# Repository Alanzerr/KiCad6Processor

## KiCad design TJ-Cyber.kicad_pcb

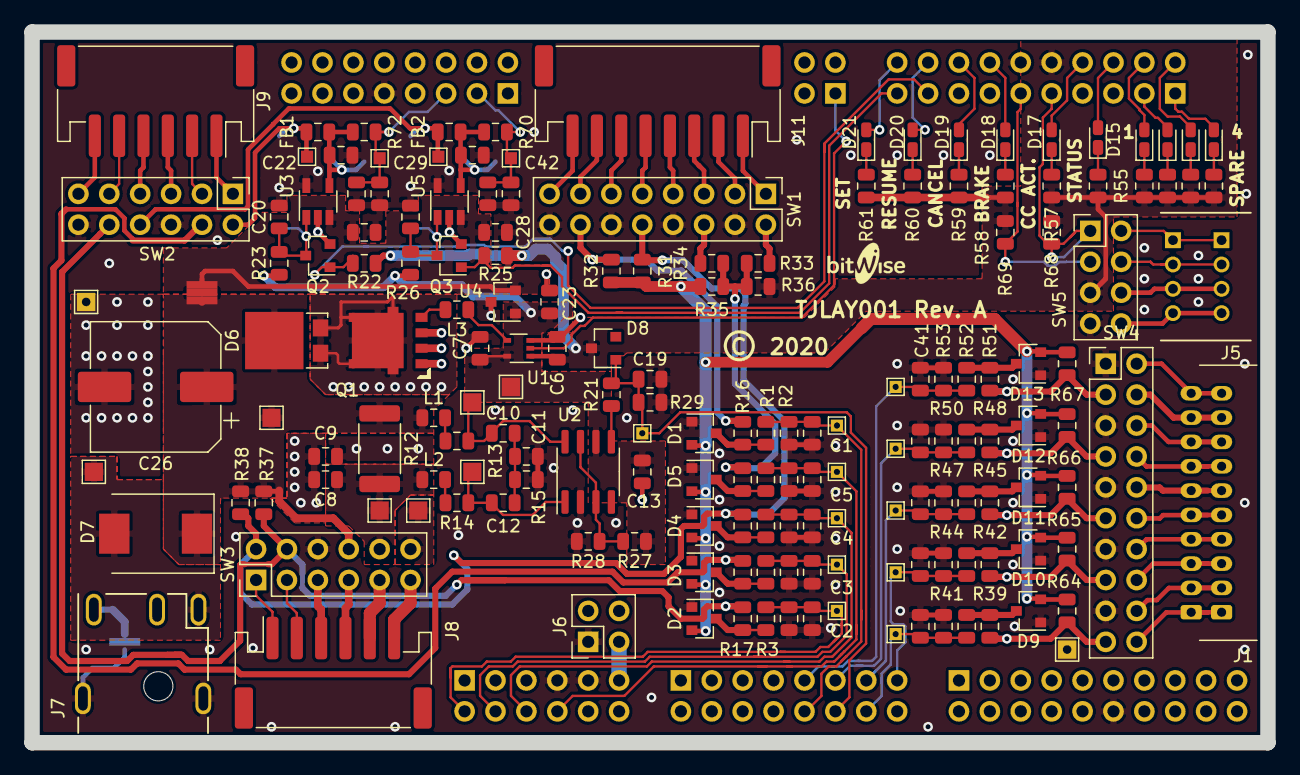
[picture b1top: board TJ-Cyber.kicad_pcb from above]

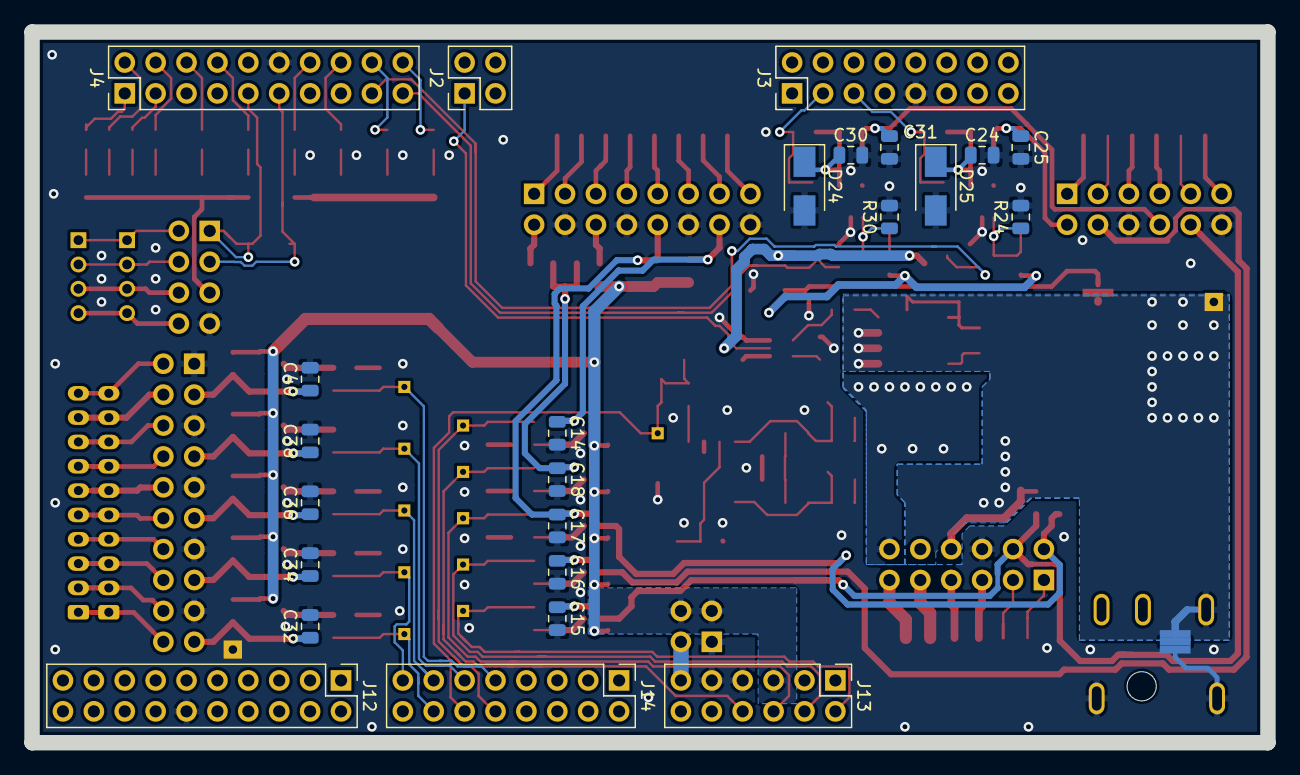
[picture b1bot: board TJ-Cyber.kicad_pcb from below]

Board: 2 copper layers, 101.6 x 58.4 mm, 235 parts (25 on the bottom side), 120 nets.

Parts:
BRD1: DNF; ProcessorStack
C1, C2, C3, C4, C5, C6, C7, C13, C20, C21, C27, C28, C33, C35, C37, C39, C41, C42, C43: 0.1uF; C_0805_2012Metric
C8, C9: 47nF; C_0805_2012Metric
C10, C12: 1nF; C_0805_2012Metric
C11, C14, C15, C16, C17, C18, C24, C25, C30, C31, C32, C34, C36, C38, C40: DNF; C_0805_2012Metric
C19: 390pF; C_0805_2012Metric
C22, C23, C29: 1uF; C_0805_2012Metric
C26: 100uF; CP_Elec_10x10.5
D1, D2, D3, D4, D5, D9, D10, D11, D12, D13: BAT54S; SOT-23
D6: SS8PH10; TO-277A
D7: MBRS540T3G; D_SMC
D8: BAR42FILM; SOT-23
D14: KPT-1608SURCK; LED_0603_1608Metric_Castellated
D15, D23: LSTS-C190GKT; LED_0603_1608Metric_Castellated
D16, D17, D18, D19, D20, D21, D22: LSTS-C190YKT; LED_0603_1608Metric_Castellated
D24, D25: DNF; D_SMA
FB1, FB2: 50mR; L_0805_2012Metric
J1: B10B-PH-K-S; JST_PH_B10B-PH-K_1x10_P2.00mm_Vertical_Hybrid
J2, J6: M20-9980245; PinHeader_2x02_P2.54mm_Vertical
J3, J14: M20-9980845; PinHeader_2x08_P2.54mm_Vertical
J4, J12: M20-9981045; PinHeader_2x10_P2.54mm_Vertical
J5: 110990030; Grove_1x4_P2mm_Vertical_Seeed_110990030_Hybrid
J7: PJ-051A; CUI_PJ-051A
J8, J9: S6B-PH-SM4-TB; JST_PH_S6B-PH-SM4-TB_1x06-1MP_P2.00mm_Horizontal
J11: S8B-PH-SM4-TB; JST_PH_S8B-PH-SM4-TB_1x08-1MP_P2.00mm_Horizontal
J13: M20-9980645; PinHeader_2x06_P2.54mm_Vertical
JMP1, JMP2, JMP3, JMP4, JMP5, JMP6, JMP7, JMP8, JMP9, JMP10, JMP11, JMP12, JMP13, JMP14, JMP15, JMP16, JMP17, JMP18, JMP19, JMP20, JMP21, JMP22, JMP23, JMP24, JMP25, JMP26, JMP27, JMP28, JMP29, JMP30, JMP31, JMP32, JMP33, JMP34: Shunt; Dummy_Jumper_Footprint_for_BOM
L1, L2, L3: 1KR; L_0805_2012Metric
LB1: DNF; BitwiseLogo
LB2: DNF; COPYRIGHT_2020
NT1, NT2: DNF; NetTie-2_SMD_Pad25mil
Q1: NVMFS5C460NL; DFN5
Q2, Q3: MGSF1N03LT1G; SOT-23
R1, R3, R5, R7, R9, R29, R40, R43, R46, R49, R52: 2K; R_0805_2012Metric
R2, R4, R6, R8, R10, R27, R41, R44, R47, R50, R53, R68, R69, R71, R73: 4.7K; R_0805_2012Metric
R11, R22, R25, R31, R32, R37, R38, R64, R65, R66, R67: 10K; R_0805_2012Metric
R12: 0.05R; R_2512_6332Metric
R13, R14: 10R; R_0805_2012Metric
R15: 33R; R_0805_2012Metric
R16, R17, R18, R19, R20, R39, R42, R45, R48, R51: 1.1K; R_0805_2012Metric
R21, R23, R26: 1K; R_0805_2012Metric
R24, R30: DNF; R_0805_2012Metric
R28: 100R; R_0805_2012Metric
R33, R35: 330R; R_0805_2012Metric
R34, R36: 680R; R_0805_2012Metric
R54, R56, R57, R58, R59, R60, R61, R62: 270R; R_0805_2012Metric
R55, R63: 220R; R_0805_2012Metric
R70, R72: 3.3K; R_0805_2012Metric
SW1: M20-9980845; PinHeader_2x08_P2.54mm_Vertical_Shunts
SW2, SW3: M20-9980645; PinHeader_2x06_P2.54mm_Vertical_Shunts
SW4: M20-9981045; PinHeader_2x10_P2.54mm_Vertical_Shunts
SW5: M20-9980445; PinHeader_2x04_P2.54mm_Vertical_Shunts
TP1, TP2, TP21, TP22: DNF; TestPoint_Pad_1.0x1.0mm
TP7, TP8, TP9, TP10, TP11, TP12, TP33, TP34, TP35, TP36, TP37: DNF; TestPoint_THTPad_1.0x1.0mm_Drill0.5mm
TP13, TP14: DNF; TestPoint_THTPad_1.5x1.5mm_Drill0.7mm
TP15, TP16, TP17, TP18, TP19, TP20, TP23: DNF; TestPoint_Pad_1.5x1.5mm
U1: SN74AUP1T34DCK; SOT-353_SC-70-5
U2: AD8210; SOIC-8_3.9x4.9mm_P1.27mm
U3, U5: NCV4250−2CSNT1G; TSOT-23-5
U4: ZMR500F; SOT-23

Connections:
+3V3: C6.1, D8.3, J4.10, R22.1, R25.1, R54.1, R55.1, R56.1, R57.1, R58.1, R59.1, R60.1, R61.1, R62.1, R63.1, R68.1, R69.1, SW5.5, U1.1
+5V: C7.1, C13.1, C23.1, R23.1, R26.1, R27.1, TP23.1, U1.5, U2.6, U4.1
+5VA: D1.2, D2.2, D3.2, D4.2, D5.2, D9.2, D10.2, D11.2, D12.2, D13.2, J6.2, J6.4, J13.5, R11.1, R31.1, R32.1, R35.1, R64.1, R65.1, R66.1, R67.1
+12C: J6.3, J13.11
+12LF: C21.1, C28.1, NT1.2, U3.3, U4.2, U5.3
+12V: C26.1, D6.3, D7.1, L1.1, NT1.1, R12.1, R37.1, R38.1, SW3.8, TP20.1
+BATT: D7.2, J7.1, TP15.1
/ADC_CH1: C18.1, R20.2, R33.1, R34.1, R35.2, R36.1
/ADC_CH2: C17.1, R19.2, R31.2, R38.2, SW1.10, SW3.2
/ADC_CH3: C16.1, R18.2, SW2.4
/ADC_CH4: C15.1, R17.2, R37.2, SW2.10, SW3.4
/ADC_CH5: C14.1, R16.2, R32.2, SW1.14
/ADC_CH6: C40.1, R51.2, R67.2, SW4.3
/ADC_CH7: C38.1, R48.2, R66.2, SW4.7
/ADC_CH8: C36.1, R45.2, R65.2, SW4.11
/ADC_CH9: C34.1, R42.2, R64.2, SW4.15
/ADC_CH10: C32.1, R11.2, R39.2, SW4.19
/BRAKE: J11.7, SW1.13
/BRAKE_GND: J11.8, SW1.15
/CANCEL: J11.5, SW1.9
/CANCEL_GND: J11.6, SW1.11
/DRIVE+: C8.1, L2.1, R12.2, SW3.10, TP16.1
/DRIVE-: C9.1, D6.1, D6.2, Q1.5, SW3.12, TP17.1
/Driver/FIL_PWM: L3.2, Q1.4
/Driver/I_OUT: R21.1, U2.5
/Driver/I_SENSE+: C10.1, R13.1, TP18.1, U2.8
/Driver/I_SENSE-: C12.1, R14.1, TP19.1, U2.1
/Driver/PWM: L3.1, U1.4
/Driver/VREF: R27.2, R28.1, U2.3, U2.7
/GGND: J5.4, SW5.8
/GPWR: J5.3, SW5.6
/GSCL: J5.1, SW5.2
/GSDA: J5.2, SW5.4
/HallSensorAVout: J8.2, SW3.3
/HallSensorBVout: J8.1, SW3.1
/HallSensorGnd: J8.3, SW3.5
/HallSensorVcc: J8.4, SW3.7
/Motor+: J8.5, SW3.9
/Motor-: J8.6, SW3.11
/PA6_PWM: J2.1, U1.2
/PC10_STATUS_LED: D15.2, J4.6
/PC11_CCA_LED: D17.2, J4.8
/PD0_ADC1_P[4]: C1.1, J14.10, R1.2, R2.1, TP11.1
/PD1_ADC1_P[5]: C19.1, D8.1, J14.12, R21.2, R29.1, TP12.1
/PD2_ADC1_P[6]: C33.1, J14.14, R40.2, R41.1, TP33.1
/PE0_CANCEL_LED: D19.2, J4.16
/PE1_BRAKE_LED: D18.2, J4.14
/PE4_RESUME_LED: D20.2, J4.18
/PE5_SET_LED: D21.2, J4.20
/PF0_ADC0_S[8]: C42.1, J3.3, R70.2, R71.1, TP1.1
/PF1_PSU1_ADC0_S[9]: C43.1, J3.5, R72.2, R73.1, TP2.1
/PF4_ADC0_S[12]: C3.1, J13.4, R5.2, R6.1, TP8.1
/PF5_ADC0_S[13]: C4.1, J13.6, R7.2, R8.1, TP9.1
/PF6_ADC0_S[14]: C2.1, J13.2, R3.2, R4.1, TP7.1
/PF7_ADC0_S[15]: C5.1, J13.8, R9.2, R10.1, TP10.1
/PF12_PSU2_ENABLE: J4.19, Q3.1, R25.2
/PF13_PSU1_ENABLE: J4.17, Q2.1, R22.2
/PG2_SPARE3_LED: D22.2, J4.2
/PG3_SPARE4_LED: D23.2, J4.1
/PG4_SPARE2_LED: D16.2, J4.3
/PG5_SPARE1_LED: D14.2, J4.4
/PI2_SDA: J4.11, R69.2, SW5.3
/PI3_SCL: J4.9, R68.2, SW5.1
/PI12_ADC0_S[20]: C41.1, J14.9, R52.2, R53.1, TP37.1
/PI13_ADC0_S[21]: C39.1, J14.11, R49.2, R50.1, TP36.1
/PI14_ADC0_S[22]: C37.1, J14.13, R46.2, R47.1, TP35.1
/PI15_ADC0_S[23]: C35.1, J14.15, R43.2, R44.1, TP34.1
/POTA_GND: J9.3, SW2.5
/POTA_INPUT: J9.2, SW2.3
/POTA_PSU: J9.1, SW2.1
/POTB_GND: J9.6, SW2.11
/POTB_INPUT: J9.5, SW2.9
/POTB_PSU: J9.4, SW2.7
/PSU1: C25.1, FB1.1, SW2.2, TP21.1
/PSU1/EN: C20.1, Q2.3, R23.2, R24.1, U3.1
/PSU1/SENSOR_POWER: C22.1, C24.1, D25.1, FB1.2, R72.1, U3.4
/PSU2: C31.1, FB2.1, SW2.8, TP22.1
/PSU2/EN: C27.1, Q3.3, R26.2, R30.1, U5.1
/PSU2/SENSOR_POWER: C29.1, C30.1, D24.1, FB2.2, R70.1, U5.4
/RESUME: J11.3, SW1.5
/RESUME_GND: J11.4, SW1.7
/RI: R34.2, SW1.6
/SET: J11.1, SW1.1
/SET_GND: J11.2, SW1.3
/SI: R33.2, SW1.2
/SPARE1: J1.9, SW4.4
/SPARE1_GND: J1.10, SW4.2
/SPARE2: J1.7, SW4.8
/SPARE2_GND: J1.8, SW4.6
/SPARE3: J1.5, SW4.12
/SPARE3_GND: J1.6, SW4.10
/SPARE4: J1.3, SW4.16
/SPARE4_GND: J1.4, SW4.14
/SPARE5: J1.1, SW4.20
/SPARE5_GND: J1.2, SW4.18
GND: C1.2, C2.2, C3.2, C4.2, C5.2, C6.2, C7.2, C11.2, C13.2, C14.2, C15.2, C16.2, C17.2, C18.2, C19.2, C20.2, C21.2, C22.2, C23.2, C24.2, C25.2, C27.2, C28.2, C29.2, C30.2, C31.2, C32.2, C33.2, C34.2, C35.2, C36.2, C37.2, C38.2, C39.2, C40.2, C41.2, C42.2, C43.2, D1.1, D2.1, D3.1, D4.1, D5.1, D9.1, D10.1, D11.1, D12.1, D13.1, D24.2, D25.2, J3.9, J4.12, J6.1, J7.5, J7.6, J12.12, J13.7, J13.9, NT2.2, Q2.2, Q3.2, R2.2, R4.2, R6.2, R8.2, R10.2, R15.2, R24.2, R28.2, R29.2, R30.2, R36.2, R41.2, R44.2, R47.2, R50.2, R53.2, R71.2, R73.2, SW1.4, SW1.8, SW1.12, SW1.16, SW2.6, SW2.12, SW3.6, SW4.1, SW4.5, SW4.9, SW4.13, SW4.17, SW5.7, TP13.1, U1.3, U2.2, U3.2, U3.5, U4.3, U5.2, U5.5
GNDPWR: C8.2, C9.2, C26.2, J7.2, NT2.1, Q1.1, Q1.2, Q1.3, TP14.1
unnamed: C10.2, C11.1, C12.2, R15.1
unnamed: D1.3, R1.1, R16.1
unnamed: D2.3, R3.1, R17.1
unnamed: D3.3, R5.1, R18.1
unnamed: D4.3, R7.1, R19.1
unnamed: D5.3, R9.1, R20.1
unnamed: D9.3, R39.1, R40.1
unnamed: D10.3, R42.1, R43.1
unnamed: D11.3, R45.1, R46.1
unnamed: D12.3, R48.1, R49.1
unnamed: D13.3, R51.1, R52.1
unnamed: D14.1, R54.2
unnamed: D15.1, R55.2
unnamed: D16.1, R56.2
unnamed: D17.1, R57.2
unnamed: D18.1, R58.2
unnamed: D19.1, R59.2
unnamed: D20.1, R60.2
unnamed: D21.1, R61.2
unnamed: D22.1, R62.2
unnamed: D23.1, R63.2
unnamed: L1.2, R13.2
unnamed: L2.2, R14.2

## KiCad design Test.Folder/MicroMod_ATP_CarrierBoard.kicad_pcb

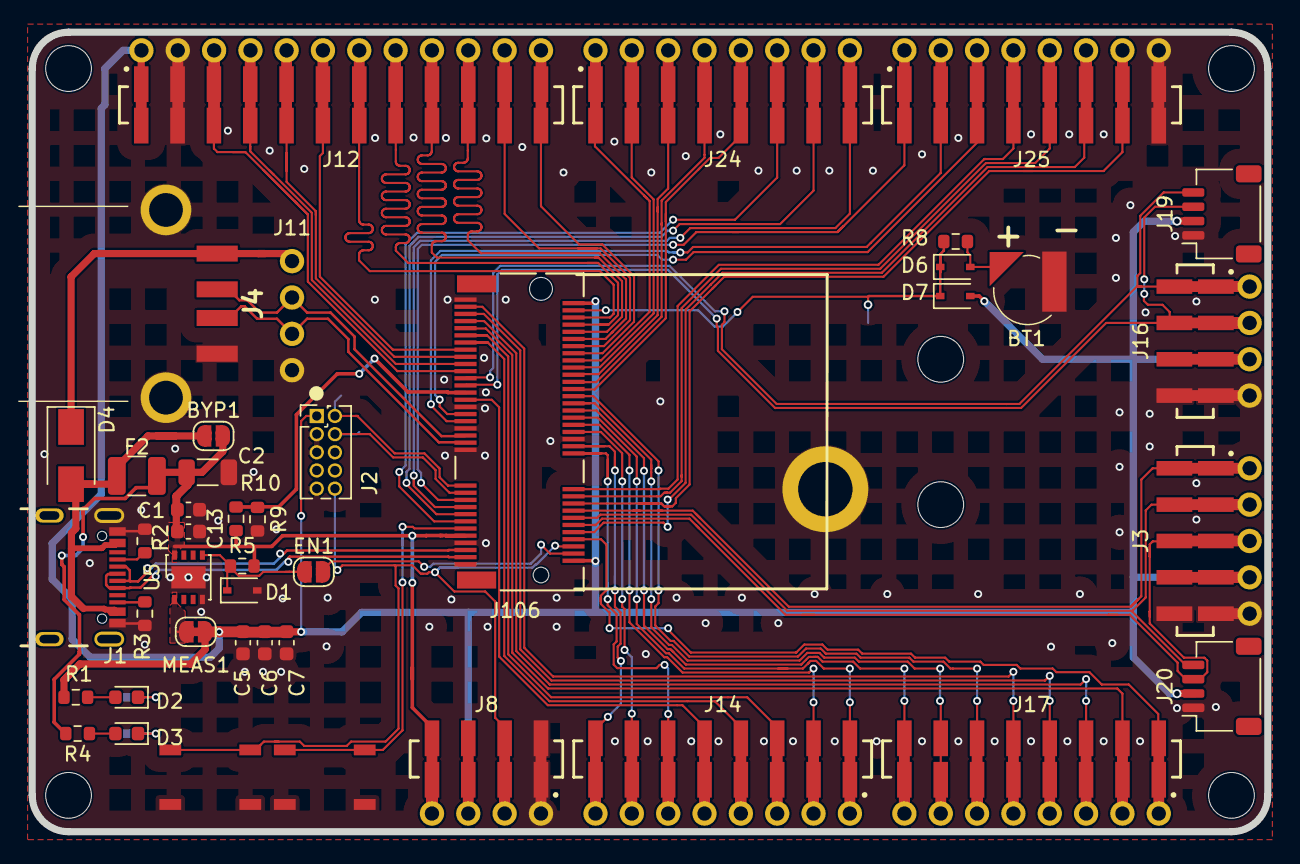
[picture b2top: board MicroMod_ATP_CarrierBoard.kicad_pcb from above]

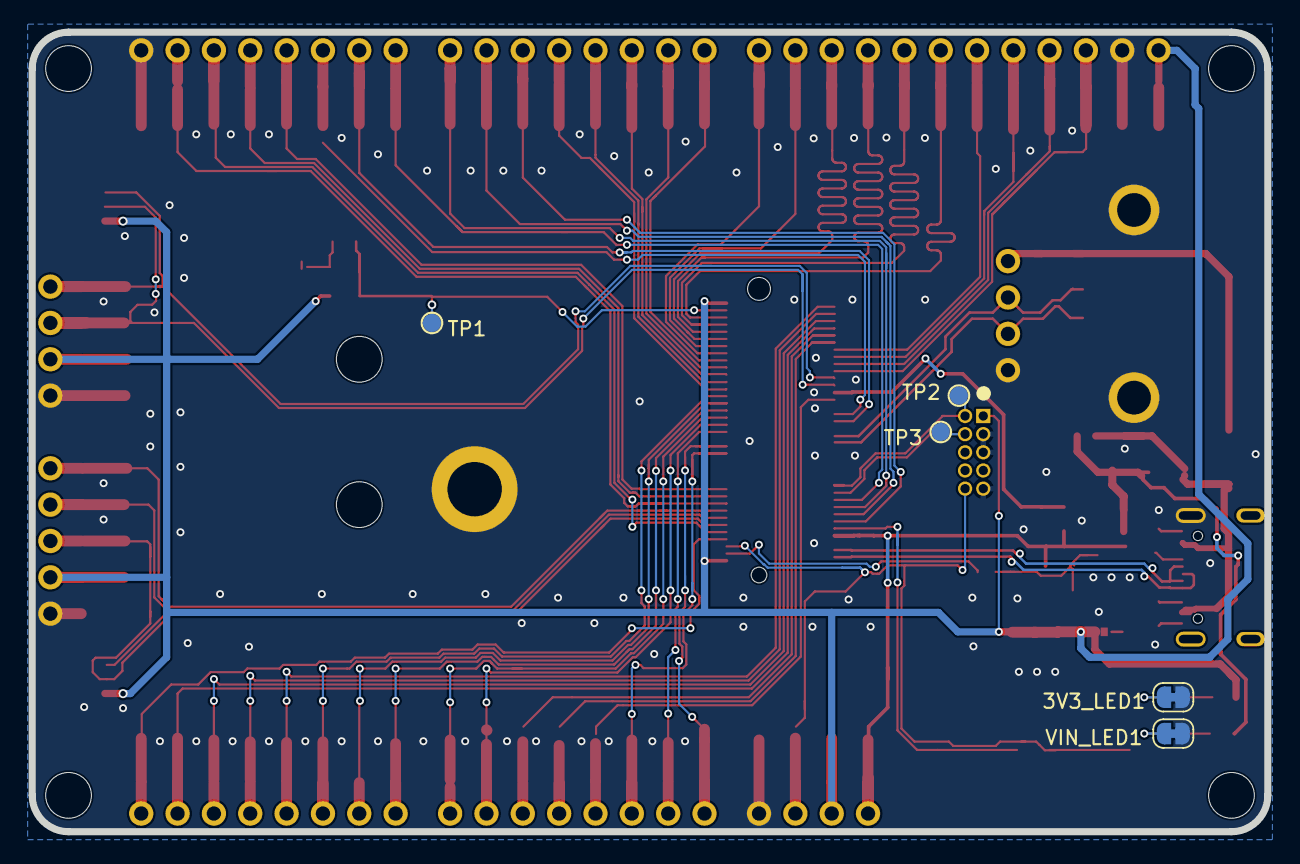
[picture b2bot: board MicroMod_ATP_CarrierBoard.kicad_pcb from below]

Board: 2 copper layers, 86.4 x 55.9 mm, 64 parts (5 on the bottom side), 71 nets.

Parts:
3V3_LED1: JUMPER-SMT_2_NC_TRACE_SILK; SolderJumper-2_P1.3mm_Bridged_RoundedPad1.0x1.5mm
BT1: ML414H; ML414H_IV01E
BYP1: JUMPER-SMT_2_NO_SILK; SolderJumper-2_P1.3mm_Open_RoundedPad1.0x1.5mm
C1, C6: 0.1uF; C_0603_1608Metric
C2: 10uF; C_1206_3216Metric
C5: 1uF; C_0603_1608Metric
C7, C13: 0.22uF; C_0603_1608Metric
D1: MM3Z3V3T1G; D_SOD-323
D2, D3: RED; LED_0603_1608Metric
D4: LSM115JE3; D_SMA
D6: BAT60A; D_SOD-323
D7: BAT20J; D_SOD-323
EN1: JUMPER-SMT_2_NO_SILK; SolderJumper-2_P1.3mm_Open_RoundedPad1.0x1.5mm
F2: 1210L200PR; Fuse_1210_3225Metric
H1, H2, H3, H4, H5, H6: STAND-OFF; MountingHole_3.2mm_M3
J1: USB_C_Receptacle_USB2.0; GCT_USB4105-GF-A_SFP
J2: Conn_02x05_Odd_Even; PinHeader_2x05_P1.27mm_Vertical
J3: Conn_01x05_Female; GCT_BG125-05-X-2-1-0420-x-x
J4: USB_B; 875832010RLF_SFP
J8, J16: Conn_01x04_Female; GCT_BG125-04-X-2-1-0420-x-x
J9, J11, J21, J22: Conn_01x04; PinHeader_1x04_P2.54mm_Vertical
J10: Conn_01x05; PinHeader_1x05_P2.54mm_Vertical
J12: Conn_01x12_Female; GCT_BG125-12-X-2-1-0420-x-x
J13, J15, J18, J23, J26: Conn_01x08; PinHeader_1x08_P2.54mm_Vertical
J14, J17, J24, J25: Conn_01x08_Female; GCT_BG125-08-X-2-1-0420-x-x
J19, J20: SH_SM04B-SRSS-TB; JST_SH_SM04B-SRSS-TB_1x04-1MP_P1.00mm_Horizontal_SFP
J106: MICROMOD-2222-C; 2199230-4
MEAS1: JUMPER-COMBO_2_NC_TRACE; SolderJumper-2_P1.3mm_Bridged_RoundedPad1.0x1.5mm
R1, R4, R8: 1K; R_0603_1608Metric
R2, R3: 5K1; R_0603_1608Metric
R5: 100K; R_0603_1608Metric
R9: 10K; R_0603_1608Metric
R10: 20K; R_0603_1608Metric
S1, S2: 431181015816; TACTILE_SWITCH_SMD_5.2MM
S3: M.2_StandOff; Dummy_Part
TP1, TP2, TP3: TestPoint; TestPoint_Pad_D1.27mm
U5: AP7361C-33FGE-7; DFN-8-1EP_3x3mm_P0.65mm_EP1.55x2.4mm
VIN_LED1: JUMPER-SMT_2_NC_TRACE_SILK; SolderJumper-2_P1.3mm_Bridged_RoundedPad1.0x1.5mm

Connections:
+3V3: C5.1, C6.1, C7.1, D7.2, J2.1, J3.4, J8.3, J9.2, J10.4, J12.1, J16.3, J19.2, J20.2, J21.3, J22.1, J106.2, J106.74, MEAS1.2, R1.2
/3.3V_EN: D1.1, EN1.1, R5.1, U5.5
/A0: J14.8, J15.8, J106.34
/A1: J14.7, J15.7, J106.38
/CAN_RXI: J25.2, J26.2, J106.41
/CAN_TXO: J25.3, J26.3, J106.43
/CIPO: J12.6, J13.7, J106.61
/CIPO1/DAT0: J12.10, J13.3, J106.64
/COPI: J12.5, J13.8, J106.59
/COPI1: J12.11, J13.2, J106.62
/CTS1: J23.7, J24.7, J106.15
/D0: J25.6, J26.6, J106.10
/D1: J25.7, J26.7, J106.18
/DAT1: J12.9, J13.4, J106.66
/DAT2: J12.8, J13.5, J106.68
/G0: J14.2, J15.2, J106.40
/G1: J14.1, J15.1, J106.42
/G2: J17.8, J18.8, J106.44
/G3: J17.7, J18.7, J106.46
/G4: J17.6, J18.6, J106.48
/G5: J17.5, J18.5, J106.73
/G6: J17.4, J18.4, J106.71
/G7: J17.3, J18.3, J106.69
/G8: J17.2, J18.2, J106.67
/G9/ADC_N: J14.3, J15.3, J106.65
/G10/ADC_P: J14.4, J15.4, J106.63
/G11: J17.1, J18.1, J106.8
/I2C_~INT: J3.1, J10.1, J106.16
/I2S_CLK: J23.5, J24.5, J106.50
/I2S_SDI: J23.3, J24.3, J106.54
/I2S_SDO: J23.2, J24.2, J106.56
/I2S_WS: J23.4, J24.4, J106.52
/MCLK: J23.1, J24.1, J106.58
/PWM0: J14.6, J15.6, J106.32
/PWM1: J14.5, J15.5, J106.47
/RTC_3V: D6.1, D7.1, J106.72, R8.2, TP1.1
/RTS1: J23.6, J24.6, J106.13
/RX1: J25.1, J26.1, J106.19
/RX2: J25.5, J26.5, J106.20
/SCK: J12.4, J22.4, J106.57
/SCK1: J12.12, J13.1, J106.60
/SCL: J3.2, J10.2, J20.4, J106.14
/SCL1: J16.1, J19.4, J21.1, J106.53
/SDA: J3.3, J10.3, J20.3, J106.12
/SDA1: J16.2, J19.3, J21.2, J106.51
/SWDCK: J2.4, J106.21, TP3.1
/SWDIO: J2.2, J106.23, TP2.1
/TX1: J23.8, J24.8, J106.17
/TX2: J25.4, J26.4, J106.22
/USBHOST_N: J4.2, J11.2, J106.37
/USBHOST_P: J4.3, J11.3, J106.35
/USB_N: J1.A7, J1.B7, J106.5
/USB_P: J1.A6, J1.B6, J106.3
/VIN_DIV3: J106.49, R9.2, R10.1
/~BOOT: J106.11, S2.3, S2.4
/~CS1/DAT3: J12.7, J13.6, J106.70
/~CS: J12.3, J22.3, J106.55
/~RESET: J2.10, J8.2, J9.3, J106.6, S1.3, S1.4
GND: 3V3_LED1.2, BT1.2, C1.2, C2.2, C5.2, C6.2, C7.2, C13.2, D1.2, J1.A1, J1.A12, J1.B1, J1.B12, J1.S1, J2.3, J2.5, J2.9, J3.5, J4.4, J4.5, J8.1, J9.4, J10.5, J11.4, J12.2, J16.4, J19.1, J20.1, J21.4, J22.2, J25.8, J26.8, J106.1, J106.7, J106.33, J106.36, J106.39, J106.45, J106.75, J106.80, R2.1, R3.1, R9.1, S1.1, S1.2, S2.1, S2.2, U5.4, U5.9, VIN_LED1.2
unnamed: 3V3_LED1.1, D2.1
unnamed: BT1.1, D6.2, R8.1
unnamed: D2.2, R1.1
unnamed: D3.1, VIN_LED1.1
unnamed: D3.2, R4.1
unnamed: EN1.2, J106.4
unnamed: J1.A5, R2.2
unnamed: J1.B5, R3.2
unnamed: MEAS1.1, U5.1
VBUS: D4.1, J4.1, J11.1
VIN: BYP1.2, C1.1, C2.1, C13.1, F2.1, J8.4, J9.1, J106.9, R4.2, R5.2, R10.2, U5.8
VUSB: BYP1.1, D4.2, F2.2, J1.A4, J1.A9, J1.B4, J1.B9

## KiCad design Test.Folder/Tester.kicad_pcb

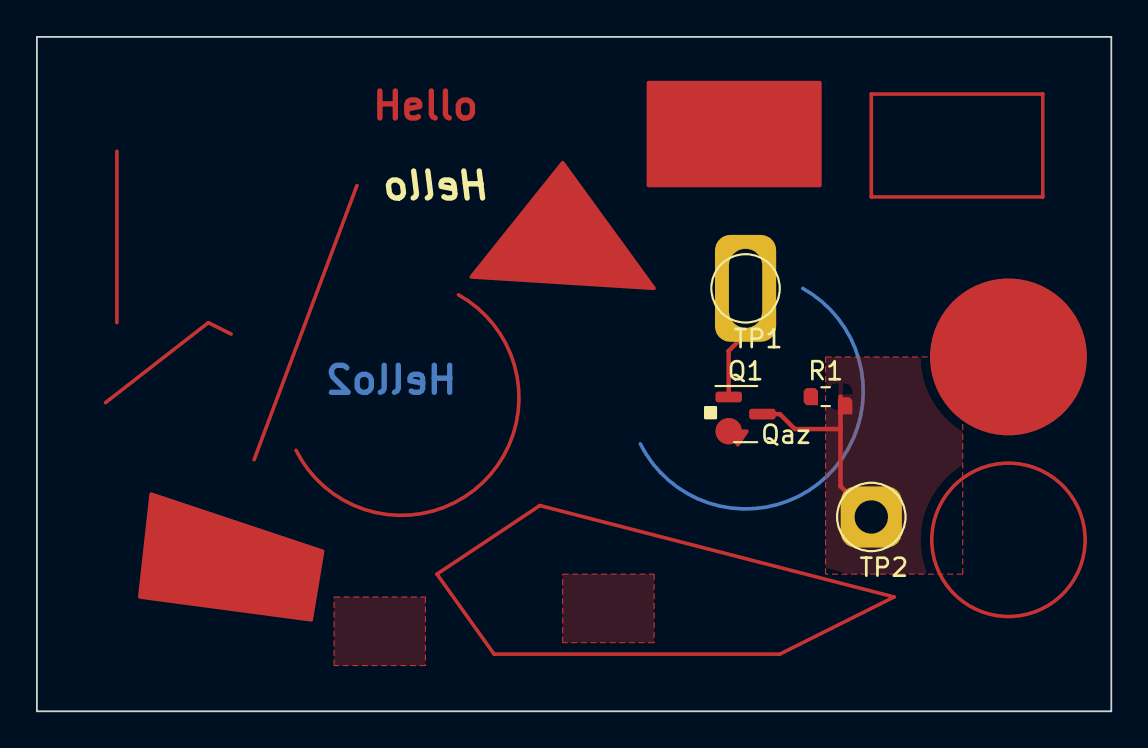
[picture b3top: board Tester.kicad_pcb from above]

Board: 4 copper layers, 59.7 x 37.5 mm, 4 parts (0 on the bottom side), 2 nets.

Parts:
Q1: Si2319CDS; SOT-23
R1: 1K; R_0603_1608Metric
TP1, TP2: TestPoint; TestPoint_Loop_D2.50mm_Drill1.85mm

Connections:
unnamed: Q1.1 (G), TP1.1
unnamed: Q1.3 (D), R1.2, TP2.1

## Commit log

2022-09-22 Basic program - allows user to select file opens and closes it!
2022-09-22 Can now input all file types!
2022-09-25 Re-structured so that each file type allows the selection of a task (althought most currently have none beyond saving the input file). PCB has an example of adding options albeit none of them actuall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
2022-10-22 Can now print the print a footprint!
2022-10-23 Added structure to support printing all elements, albeit can only print footprints!
2022-10-27 Can print everything except board, schematics and symbols
2022-10-28 Can print everything except board, and schematics
2022-11-05 Can print everything - about to change GUI
2022-11-09 GUI Updates to input files, allow user to inspect and then save (or not).
2022-11-09 Updated to ignore KiCAD files.
2022-12-03 Can 1. output a kiCad file, 2. update the libray 3. add the footprint and models correctly 4. add the model of the original board
    Can't
    1. draw silkscreen for connectors
    2. generate the symbol
2022-12-10 Can 1. output a kiCad file 2. update the libray 3. add the footprint and models correctly 4. add the model of the original board 5. draw silkscreen for connectors
    Can't
    1. generate the symbol
    2. copy required 3D data to new library
    3. optimised center
    4. optimised grow function
2022-12-18 Can 1. Output a kiCad file 2. Update the libray 3. Add the footprint and models correctly 4. Add the model of the original board 5. Draw silkscreen for connectors 6. Differentiate outline from non-ou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
    Can't
    1. Generate the symbol
    2. Copy required 3D data to new library
    3. Optimised grow function
    4. Draw silkscreen and courtyard
2022-12-30 Can 1. Output a kiCad file 2. Update the libray 3. Add the footprint and models correctly 4. Add the model of the original board 5. Draw silkscreen for connectors 6. Differentiate outline from non-ou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
    Can't
    1. Generate the symbol
    2. Copy required 3D data to new library
    3. Optimised grow function - so commented out all code for now
    4. Draw silkscreen and courtyard - becasue of 3, - commented out all code for now
2022-12-31 Can 1. Output a kiCad file 2. Update the libray 3. Add the footprint and models correctly 4. Add the model of the original board 5. Draw silkscreen for connectors 6. Differentiate outline from non-ou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
    Can't
    1. Copy required 3D data to new library
    2. Optimised grow function - so commented out all code for now
    3. Draw silkscreen and courtyard - becasue of 3, - commented out all code for now
2023-01-01 Can 1. Output a kiCad file 2. Update the libray 3. Add the footprint and models correctly 4. Add the model of the original board 5. Draw silkscreen for connectors 6. Differentiate outline from non-ou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
    Can't
    1. Copy required 3D data to new library - it is not clear that this is required!
    2. Optimised grow function - so commented out all code for now
    3. Draw silkscreen and courtyard - because of 3, - commented out all code for now
2023-01-01 Can 1. Output a kiCad file 2. Update the libray 3. Add the footprint and models correctly 4. Add the model of the original board 5. Draw silkscreen for connectors 6. Differentiate outline from non-ou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
    Can't
    1. Copy required 3D data to new library - it is not clear that this is required!
    2. Optimised grow function - so commented out all code for now
    3. Draw silkscreen and courtyard - because of 3, - commented out all code for now
    Fixes
    1. Minor tidy-ups to fix prints.

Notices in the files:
parts and their libraries:
Copyright 2020 for use on PCBs.
